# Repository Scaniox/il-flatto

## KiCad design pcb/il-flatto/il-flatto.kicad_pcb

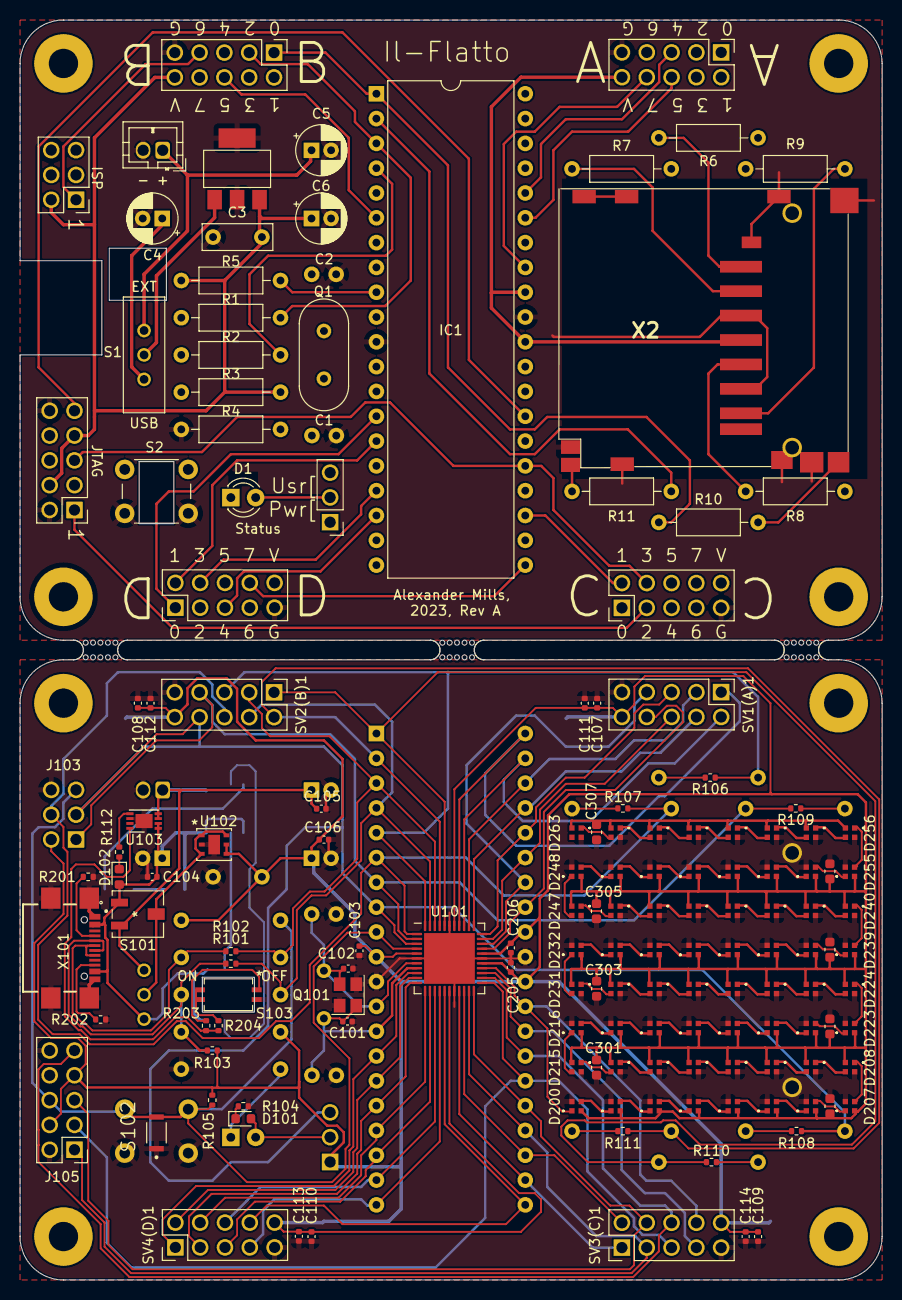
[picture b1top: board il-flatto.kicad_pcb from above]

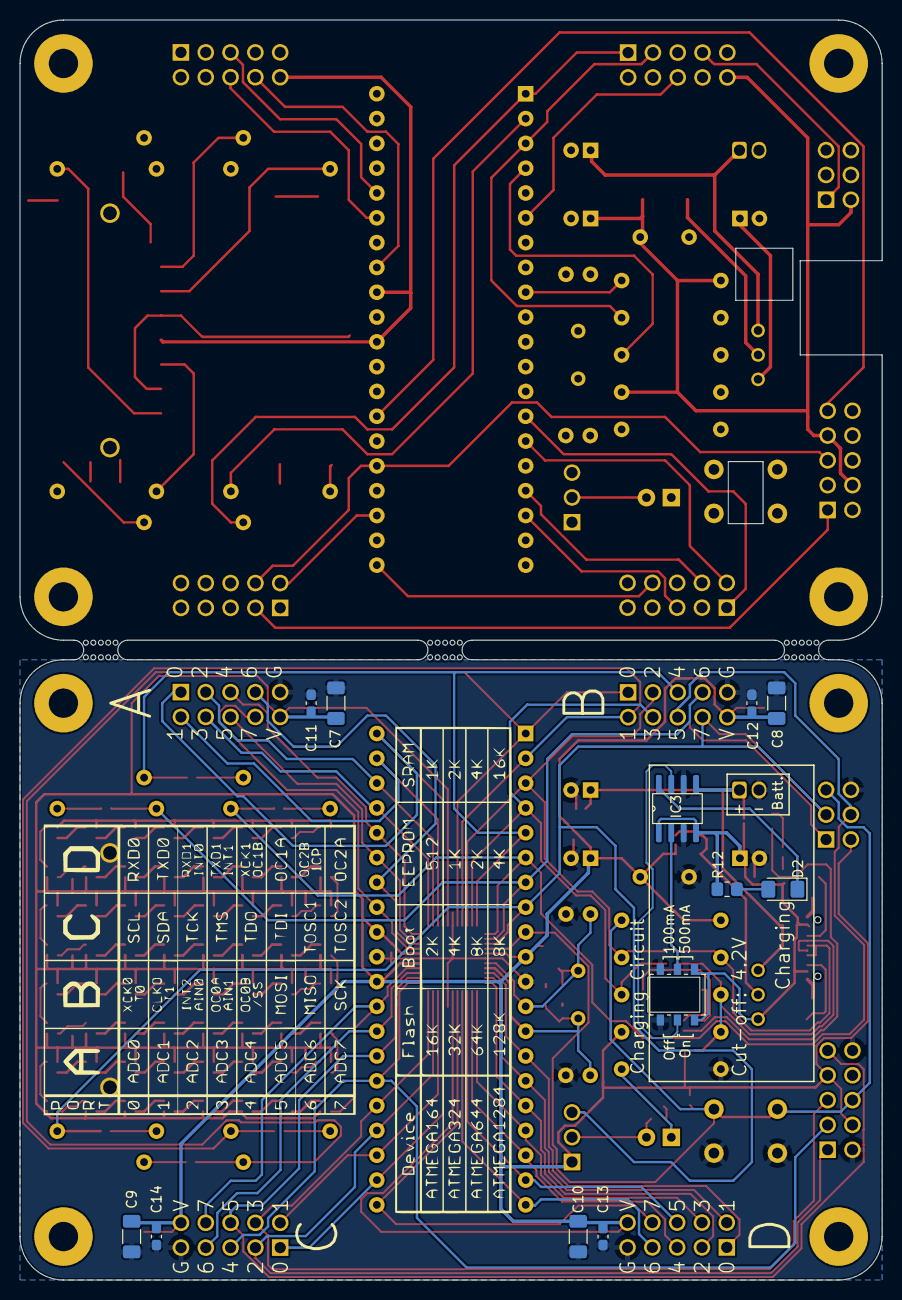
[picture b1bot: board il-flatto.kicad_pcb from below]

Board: 2 copper layers, 88.3 x 129.0 mm, 191 parts (12 on the bottom side), 126 nets.

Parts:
C1, C1#2, C2, C2#2: 22pf; C_Disc_D3.8mm_W2.6mm_P2.50mm
C3, C3#2: 100nf; C_Disc_D7.0mm_W2.5mm_P5.00mm
C4, C4#2, C5, C5#2: 10uf; CP_Radial_D5.0mm_P2.00mm
C6, C6#2: 100uf; CP_Radial_D5.0mm_P2.00mm
C7, C8, C9, C10: 10uf; C_1206_3216Metric_Pad1.33x1.80mm_HandSolder
C11, C12, C13, C14: 100nf; C_0603_1608Metric_Pad1.08x0.95mm_HandSolder
C101, C102: 22pf; C_0402_1005Metric
C103, C111, C112, C113, C114, C205, C206: 100nf; C_0402_1005Metric
C104, C105, C106, C107, C108, C109, C110: 10uf; C_0402_1005Metric
C300, C301, C302, C303, C304, C305, C306, C307: 10u; C_0603_1608Metric
D1, D1#2: LED; LED_D3.0mm
D2: CHRG; LED_1206_3216Metric_Pad1.42x1.75mm_HandSolder
D101: LED; LED_0603_1608Metric
D102: CHRG; LED_0603_1608Metric
D200, D201, D202, D203, D204, D205, D206, D207, D208, D209, D210, D211, D212, D213, D214, D215, D216, D217, D218, D219, D220, D221, D222, D223, D224, D225, D226, D227, D228, D229, D230, D231, D232, D233, D234, D235, D236, D237, D238, D239, D240, D241, D242, D243, D244, D245, D246, D247, D248, D249, D250, D251, D252, D253, D254, D255, D256, D257, D258, D259, D260, D261, D262, D263: IN-PI15TAT5R5G5B; INPI15TAT5R5G5B
IC1: ATmega1284P-P; DIP-40_W15.24mm
IC2: MCP1825S; SOT-223-3_TabPin2
IC3: MAX1811; SOIC-8_3.9x4.9mm_P1.27mm
J3, J103: ISP; PinSocket_2x03_P2.54mm zero footprint mirror
J5, J105: JTAG; PinSocket_2x05_P2.54mm zero footprint mirror
JP3, JP103: Conn_01x03; PinHeader_1x03_P2.54mm zero footprint
Q1, Q1#2: 12MHz; Crystal_HC49-4H_Vertical
Q101: 12MHz; Crystal_SMD_Abracon_ABM8G-4Pin_3.2x2.5mm
R1, R1#2, R2, R2#2, R6, R6#2, R7, R7#2, R8, R8#2, R9, R9#2, R10, R10#2, R11, R11#2: 68; R_Axial_DIN0207_L6.3mm_D2.5mm_P10.16mm_Horizontal
R3, R3#2: 1.5k; R_Axial_DIN0207_L6.3mm_D2.5mm_P10.16mm_Horizontal
R4, R4#2: 220; R_Axial_DIN0207_L6.3mm_D2.5mm_P10.16mm_Horizontal
R5, R5#2: 10k; R_Axial_DIN0207_L6.3mm_D2.5mm_P10.16mm_Horizontal
R12: 330; R_0805_2012Metric_Pad1.20x1.40mm_HandSolder
R101, R102, R106, R107, R108, R109, R110, R111: 68; R_0402_1005Metric
R103: 1.5k; R_0402_1005Metric
R104: 220; R_0402_1005Metric
R105, R204: 10k; R_0402_1005Metric
R112: 470; R_0402_1005Metric
R201, R202: 5.1k; R_0402_1005Metric
R203: 2.5k; R_0402_1005Metric
S1, S1#2: S1; EG1218
S2, S2#2: SW_SPST; SW_PUSH_6mm
S3: 0; CAS-D20TB
S101: PWR SEL; CS-4-12XA
S102: SW_SPST; SW_TL3780AF240QG
S103: SW_DPST_x2; CVS-02TB mirrored
SV1(A)1, SV1(A)1#2, SV2(B)1, SV2(B)1#2, SV3(C)1, SV3(C)1#2, SV4(D)1, SV4(D)1#2: Conn_02x05_Odd_Even; PinSocket_2x05_P2.54mm zero footprint mirror
U101: ATmega1284P-M; QFN-44-1EP_7x7mm_P0.5mm_EP5.2x5.2mm
U102: NCV8605MN33T2G
U103: MCP73831-2-MC; DFN-8-1EP_3x2mm_P0.5mm_EP1.75x1.45mm
X2, X102: SD_Card; sd card
X3, X103: BAT; JST_PH_B2B-PH-K_1x02_P2.00mm_Vertical
X101: USB_C_Receptacle_USB2.0; GCT_USB4110-GF-A_REVB
mouse-bite-3mm-slot, mouse-bite-3mm-slot#2, mouse-bite-3mm-slot#3: VAL**; mouse-bite-3mm-slot

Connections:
/internals/Row1/DOUT: D207.1 (DOUT), D208.3 (DIN)
/internals/Row2/DOUT: D215.1 (DOUT), D216.3 (DIN)
/internals/Row3/DOUT: D223.1 (DOUT), D224.3 (DIN)
/internals/Row4/DOUT: D231.1 (DOUT), D232.3 (DIN)
/internals/Row5/DOUT: D239.1 (DOUT), D240.3 (DIN)
/internals/Row6/DOUT: D247.1 (DOUT), D248.3 (DIN)
/internals/Row7/DOUT: D255.1 (DOUT), D256.3 (DIN)
GND: C1.1, C1#2.1, C2.1, C2#2.1, C3.2, C3#2.2, C4.2, C4#2.2, C5.2, C5#2.2, C6.2, C6#2.2, C7.2, C8.2, C9.2, C10.2, C11.2, C12.2, C13.2, C14.2, C101.1, C102.1, C103.2, C104.1, C105.1, C106.1, C107.2, C108.2, C109.2, C110.2, C111.2, C112.2, C113.2, C114.2, C205.2, C206.2, C300.2, C301.2, C302.2, C303.2, C304.2, C305.2, C306.2, C307.2, D200.4 (VSS), D201.4 (VSS), D202.4 (VSS), D203.4 (VSS), D204.4 (VSS), D205.4 (VSS), D206.4 (VSS), D207.4 (VSS), D208.4 (VSS), D209.4 (VSS), D210.4 (VSS), D211.4 (VSS), D212.4 (VSS), D213.4 (VSS), D214.4 (VSS), D215.4 (VSS), D216.4 (VSS), D217.4 (VSS), D218.4 (VSS), D219.4 (VSS), D220.4 (VSS), D221.4 (VSS), D222.4 (VSS), D223.4 (VSS), D224.4 (VSS), D225.4 (VSS), D226.4 (VSS), D227.4 (VSS), D228.4 (VSS), D229.4 (VSS), D230.4 (VSS), D231.4 (VSS), D232.4 (VSS), D233.4 (VSS), D234.4 (VSS), D235.4 (VSS), D236.4 (VSS), D237.4 (VSS), D238.4 (VSS), D239.4 (VSS), D240.4 (VSS), D241.4 (VSS), D242.4 (VSS), D243.4 (VSS), D244.4 (VSS), D245.4 (VSS), D246.4 (VSS), D247.4 (VSS), D248.4 (VSS), D249.4 (VSS), D250.4 (VSS), D251.4 (VSS), D252.4 (VSS), D253.4 (VSS), D254.4 (VSS), D255.4 (VSS), D256.4 (VSS), D257.4 (VSS), D258.4 (VSS), D259.4 (VSS), D260.4 (VSS), D261.4 (VSS), D262.4 (VSS), D263.4 (VSS), IC1.11 (GND), IC1.31 (GND), IC2.2 (GND), IC3.3 (GND), IC3.6 (GND), J3.6, J5.2, J5.10, J103.6, J105.2, J105.10, Q101.2, Q101.4, R4.2, R4#2.2, R104.2, R201.2, R202.2, S2.1 (A), S2#2.1 (A), S3.1 (A), S3.4 (A), S102.1 (A), S103.3 (A), SV1(A)1.9, SV1(A)1#2.9, SV2(B)1.9, SV2(B)1#2.9, SV3(C)1.9, SV3(C)1#2.9, SV4(D)1.9, SV4(D)1#2.9, U101.6 (GND), U101.18 (GND), U101.28 (GND), U101.39 (GND), U101.45 (GND), U102.2 (GND), U102.7 (EPAD), U103.6 (VSS), X2.3 (VSS), X2.6 (VSS), X2.13 (SHELL2), X3.2, X101.A1/B12 (GND), X101.B1/A12 (GND), X101.S1 (SHIELD), X101.S2 (SHIELD), X101.S3 (SHIELD), X101.S4 (SHIELD), X103.2
LDO_in: IC2.1 (VI), S1.2 (B), S1#2.2 (B), S101.2 (B), U102.1 (VIN), U102.3 (NC/EN), U102.6 (VIN)
unnamed: D1.1 (K), D1#2.1 (K), R4.1, R4#2.1
unnamed: D1.2 (A), D1#2.2 (A), JP3.2
unnamed: D2.1 (K), IC3.8 (~CHG)
unnamed: D2.2 (A), R12.2
unnamed: D101.1 (K), R104.1
unnamed: D101.2 (A), JP103.2
unnamed: D102.1 (K), R112.1
unnamed: D200.1 (DOUT), D201.3 (DIN)
unnamed: D201.1 (DOUT), D202.3 (DIN)
unnamed: D202.1 (DOUT), D203.3 (DIN)
unnamed: D203.1 (DOUT), D204.3 (DIN)
unnamed: D204.1 (DOUT), D205.3 (DIN)
unnamed: D205.1 (DOUT), D206.3 (DIN)
unnamed: D206.1 (DOUT), D207.3 (DIN)
unnamed: D208.1 (DOUT), D209.3 (DIN)
unnamed: D209.1 (DOUT), D210.3 (DIN)
unnamed: D210.1 (DOUT), D211.3 (DIN)
unnamed: D211.1 (DOUT), D212.3 (DIN)
unnamed: D212.1 (DOUT), D213.3 (DIN)
unnamed: D213.1 (DOUT), D214.3 (DIN)
unnamed: D214.1 (DOUT), D215.3 (DIN)
unnamed: D216.1 (DOUT), D217.3 (DIN)
unnamed: D217.1 (DOUT), D218.3 (DIN)
unnamed: D218.1 (DOUT), D219.3 (DIN)
unnamed: D219.1 (DOUT), D220.3 (DIN)
unnamed: D220.1 (DOUT), D221.3 (DIN)
unnamed: D221.1 (DOUT), D222.3 (DIN)
unnamed: D222.1 (DOUT), D223.3 (DIN)
unnamed: D224.1 (DOUT), D225.3 (DIN)
unnamed: D225.1 (DOUT), D226.3 (DIN)
unnamed: D226.1 (DOUT), D227.3 (DIN)
unnamed: D227.1 (DOUT), D228.3 (DIN)
unnamed: D228.1 (DOUT), D229.3 (DIN)
unnamed: D229.1 (DOUT), D230.3 (DIN)
unnamed: D230.1 (DOUT), D231.3 (DIN)
unnamed: D232.1 (DOUT), D233.3 (DIN)
unnamed: D233.1 (DOUT), D234.3 (DIN)
unnamed: D234.1 (DOUT), D235.3 (DIN)
unnamed: D235.1 (DOUT), D236.3 (DIN)
unnamed: D236.1 (DOUT), D237.3 (DIN)
unnamed: D237.1 (DOUT), D238.3 (DIN)
unnamed: D238.1 (DOUT), D239.3 (DIN)
unnamed: D240.1 (DOUT), D241.3 (DIN)
unnamed: D241.1 (DOUT), D242.3 (DIN)
unnamed: D242.1 (DOUT), D243.3 (DIN)
unnamed: D243.1 (DOUT), D244.3 (DIN)
unnamed: D244.1 (DOUT), D245.3 (DIN)
unnamed: D245.1 (DOUT), D246.3 (DIN)
unnamed: D246.1 (DOUT), D247.3 (DIN)
unnamed: D248.1 (DOUT), D249.3 (DIN)
unnamed: D249.1 (DOUT), D250.3 (DIN)
unnamed: D250.1 (DOUT), D251.3 (DIN)
unnamed: D251.1 (DOUT), D252.3 (DIN)
unnamed: D252.1 (DOUT), D253.3 (DIN)
unnamed: D253.1 (DOUT), D254.3 (DIN)
unnamed: D254.1 (DOUT), D255.3 (DIN)
unnamed: D256.1 (DOUT), D257.3 (DIN)
unnamed: D257.1 (DOUT), D258.3 (DIN)
unnamed: D258.1 (DOUT), D259.3 (DIN)
unnamed: D259.1 (DOUT), D260.3 (DIN)
unnamed: D260.1 (DOUT), D261.3 (DIN)
unnamed: D261.1 (DOUT), D262.3 (DIN)
unnamed: D262.1 (DOUT), D263.3 (DIN)
unnamed: IC3.2 (SELI), S3.5 (B)
unnamed: IC3.7 (EN), S3.2 (B)
unnamed: R6.2, R6#2.2, X2.1 (CD/DAT3)
unnamed: R7.1, R7#2.1, X2.2 (CMD)
unnamed: R8.1, R8#2.1, X2.5 (CLK)
unnamed: R9.1, R9#2.1, X2.7 (DAT0)
unnamed: R10.2, R10#2.2, X2.11 (WRITE_PROTECT)
unnamed: R11.1, R11#2.1, X2.10 (CARD_DETECT)
unnamed: R112.2, U103.5 (STAT)
unnamed: R201.1, X101.A5 (CC1)
unnamed: R202.1, X101.B5 (CC2)
unnamed: R203.1, R204.1, U103.8 (PROG)
unnamed: R203.2, S103.1 (A)
unnamed: R204.2, S103.2 (B), S103.4 (B)
PA0: IC1.40 (PA0), SV1(A)1.1, SV1(A)1#2.1, U101.37 (PA0)
PA1: IC1.39 (PA1), SV1(A)1.2, SV1(A)1#2.2, U101.36 (PA1)
PA2: IC1.38 (PA2), SV1(A)1.3, SV1(A)1#2.3, U101.35 (PA2)
PA3: IC1.37 (PA3), SV1(A)1.4, SV1(A)1#2.4, U101.34 (PA3)
PA4: IC1.36 (PA4), SV1(A)1.5, SV1(A)1#2.5, U101.33 (PA4)
PA5: IC1.35 (PA5), SV1(A)1.6, SV1(A)1#2.6, U101.32 (PA5)
PA6: IC1.34 (PA6), SV1(A)1.7, SV1(A)1#2.7, U101.31 (PA6)
PA7: IC1.33 (PA7), SV1(A)1.8, SV1(A)1#2.8, U101.30 (PA7)
PB0: IC1.1 (PB0), R10.1, R10#2.1, R110.1, SV2(B)1.1, SV2(B)1#2.1, U101.40 (PB0)
PB1: IC1.2 (PB1), R11.2, R11#2.2, R111.2, SV2(B)1.2, SV2(B)1#2.2, U101.41 (PB1)
PB2: IC1.3 (PB2), R1.2, R1#2.2, R101.1, SV2(B)1.3, SV2(B)1#2.3, U101.42 (PB2)
PB3: IC1.4 (PB3), R2.1, R2#2.1, R102.2, SV2(B)1.4, SV2(B)1#2.4, U101.43 (PB3)
PB4: IC1.5 (PB4), R6.1, R6#2.1, R106.1, SV2(B)1.5, SV2(B)1#2.5, U101.44 (PB4)
PB5: IC1.6 (PB5), J3.4, J103.4, R7.2, R7#2.2, R107.2, SV2(B)1.6, SV2(B)1#2.6, U101.1 (PB5)
PB6: IC1.7 (PB6), J3.1, J103.1, R9.2, R9#2.2, R109.2, SV2(B)1.7, SV2(B)1#2.7, U101.2 (PB6)
PB7: IC1.8 (PB7), J3.3, J103.3, JP3.3, JP103.3, R8.2, R8#2.2, R108.2, SV2(B)1.8, SV2(B)1#2.8, U101.3 (PB7)
PC0: IC1.22 (PC0), SV3(C)1.1, SV3(C)1#2.1, U101.19 (PC0)
PC1: IC1.23 (PC1), SV3(C)1.2, SV3(C)1#2.2, U101.20 (PC1)
PC2: IC1.24 (PC2), J5.1, J105.1, SV3(C)1.3, SV3(C)1#2.3, U101.21 (PC2)
PC3: IC1.25 (PC3), J5.5, J105.5, SV3(C)1.4, SV3(C)1#2.4, U101.22 (PC3)
PC4: IC1.26 (PC4), J5.3, J105.3, SV3(C)1.5, SV3(C)1#2.5, U101.23 (PC4)
PC5: IC1.27 (PC5), J5.9, J105.9, SV3(C)1.6, SV3(C)1#2.6, U101.24 (PC5)
PC6: IC1.28 (PC6), SV3(C)1.7, SV3(C)1#2.7, U101.25 (PC6)
PC7: D200.3 (DIN), IC1.29 (PC7), SV3(C)1.8, SV3(C)1#2.8, U101.26 (PC7)
PD0: IC1.14 (PD0), SV4(D)1.1, SV4(D)1#2.1, U101.9 (PD0)
PD1: IC1.15 (PD1), SV4(D)1.2, SV4(D)1#2.2, U101.10 (PD1)
PD2: IC1.16 (PD2), SV4(D)1.3, SV4(D)1#2.3, U101.11 (PD2)
PD3: IC1.17 (PD3), SV4(D)1.4, SV4(D)1#2.4, U101.12 (PD3)
PD4: IC1.18 (PD4), SV4(D)1.5, SV4(D)1#2.5, U101.13 (PD4)
PD5: IC1.19 (PD5), SV4(D)1.6, SV4(D)1#2.6, U101.14 (PD5)
PD6: IC1.20 (PD6), SV4(D)1.7, SV4(D)1#2.7, U101.15 (PD6)
PD7: IC1.21 (PD7), SV4(D)1.8, SV4(D)1#2.8, U101.16 (PD7)
Q1_1: C1.2, C1#2.2, C101.2, IC1.13 (XTAL1), Q1.2, Q1#2.2, Q101.1, U101.8 (XTAL1)
Q1_2: C2.2, C2#2.2, C102.2, IC1.12 (XTAL2), Q1.1, Q1#2.1, Q101.3, U101.7 (XTAL2)
USB D+: R1.1, R1#2.1, R101.2, X101.A6 (D+), X101.B6 (D+)
USB D-: R2.2, R2#2.2, R3.2, R3#2.2, R102.1, R103.2, X101.A7 (D-), X101.B7 (D-)
VBUS: C4.1, C4#2.1, C104.2, D102.2 (A), IC3.1 (SELV), IC3.4 (IN), R12.1, S1.1 (A), S1#2.1 (A), S3.3 (C), S3.6 (C), S101.1 (A), U103.1 (VDD), U103.2 (VDD), X101.A4/B9 (VBUS), X101.B4/A9 (VBUS)
VDD: C3.1, C3#2.1, C6.1, C6#2.1, C7.1, C8.1, C9.1, C10.1, C11.1, C12.1, C13.1, C14.1, C103.1, C106.2, C107.1, C108.1, C109.1, C110.1, C111.1, C112.1, C113.1, C114.1, C205.1, C206.1, C300.1, C301.1, C302.1, C303.1, C304.1, C305.1, C306.1, C307.1, D200.2 (VDD), D201.2 (VDD), D202.2 (VDD), D203.2 (VDD), D204.2 (VDD), D205.2 (VDD), D206.2 (VDD), D207.2 (VDD), D208.2 (VDD), D209.2 (VDD), D210.2 (VDD), D211.2 (VDD), D212.2 (VDD), D213.2 (VDD), D214.2 (VDD), D215.2 (VDD), D216.2 (VDD), D217.2 (VDD), D218.2 (VDD), D219.2 (VDD), D220.2 (VDD), D221.2 (VDD), D222.2 (VDD), D223.2 (VDD), D224.2 (VDD), D225.2 (VDD), D226.2 (VDD), D227.2 (VDD), D228.2 (VDD), D229.2 (VDD), D230.2 (VDD), D231.2 (VDD), D232.2 (VDD), D233.2 (VDD), D234.2 (VDD), D235.2 (VDD), D236.2 (VDD), D237.2 (VDD), D238.2 (VDD), D239.2 (VDD), D240.2 (VDD), D241.2 (VDD), D242.2 (VDD), D243.2 (VDD), D244.2 (VDD), D245.2 (VDD), D246.2 (VDD), D247.2 (VDD), D248.2 (VDD), D249.2 (VDD), D250.2 (VDD), D251.2 (VDD), D252.2 (VDD), D253.2 (VDD), D254.2 (VDD), D255.2 (VDD), D256.2 (VDD), D257.2 (VDD), D258.2 (VDD), D259.2 (VDD), D260.2 (VDD), D261.2 (VDD), D262.2 (VDD), D263.2 (VDD), IC1.10 (VCC), IC1.30 (AVCC), IC1.32 (AREF), IC2.3 (VO), J3.2, J5.4, J5.7, J103.2, J105.4, J105.7, JP3.1, JP103.1, R3.1, R3#2.1, R5.1, R5#2.1, R103.1, R105.1, SV1(A)1.10, SV1(A)1#2.10, SV2(B)1.10, SV2(B)1#2.10, SV3(C)1.10, SV3(C)1#2.10, SV4(D)1.10, SV4(D)1#2.10, U101.5 (VCC), U101.17 (VCC), U101.27 (AVCC), U101.29 (AREF), U101.38 (VCC), U102.4 (VOUT), U102.5 (SENSE/ADJ), X2.4 (VDD)
V_BAT: C5.1, C5#2.1, C105.2, IC3.5 (BATT), S1.3 (C), S1#2.3 (C), S101.3 (C), U103.3 (VBAT), U103.4 (VBAT), X3.1, X103.1
n_reset: IC1.9 (~RESET), J3.5, J5.6, J103.5, J105.6, R5.2, R5#2.2, R105.2, S2.2 (B), S2#2.2 (B), S102.2 (B), U101.4 (~RESET)

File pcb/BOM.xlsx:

Id | Designator | Package | populate | Quantity | Designation | Supplier | link | ordered | acquired
20 | ,,,,, |  |  | 6
38 | C1,C2,C2,C1 | C_Disc_D3.8mm_W2.6mm_P2.50mm |  | 4 | 22pf
10 | C102,C101 | C_0402_1005Metric | x | 2 | 22pf | have
14 | C108,C110,C107,C109,C106,C105,C104 | C_0402_1005Metric | x | 7 | 10uf | have
6 | C113,C205,C111,C112,C103,C114,C206 | C_0402_1005Metric | x | 7 | 100nf | have
44 | C13,C14,C11,C12 | C_0603_1608Metric_Pad1.08x0.95mm_HandSolder |  | 4 | 100nf
21 | C3,C3 | C_Disc_D7.0mm_W2.5mm_P5.00mm |  | 2 | 100nf
4 | C304,C303,C305,C307,C306,C302,C301,C300 | C_0603_1608Metric | x | 8 | 10uf | digikey | https://www.digikey.com/en/products/detail/murata-electronic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 | x
8 | C4,C5,C4,C5 | CP_Radial_D5.0mm_P2.00mm |  | 4 | 10uf
5 | C6,C6 | CP_Radial_D5.0mm_P2.00mm |  | 2 | 100uf
47 | C7,C9,C8,C10 | C_1206_3216Metric_Pad1.33x1.80mm_HandSolder |  | 4 | 10uf
33 | D1,D1 | LED_D3.0mm |  | 2 | LED
42 | D101 | LED_0603_1608Metric | x | 1 | LED | have
35 | D102 | LED_0603_1608Metric | x | 1 | CHRG | have
46 | D2 | LED_1206_3216Metric_Pad1.42x1.75mm_HandSolder |  | 1 | CHRG
2 | D210,D211,D232,D258,D250,D249,D261,D252,D227,D200,D221,D231,D206,D201,D233,D253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 | IN-PI15TAT5R5G5B | x | 64 | IN-PI15TAT5R5G5B | digikey | https://www.digikey.co.uk/en/products/detail/inolux/IN-PI15T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 | x
29 | IC1 | DIP-40_W15.24mm |  | 1 | ATmega1284P-P
34 | IC2 | SOT-223-3_TabPin2 |  | 1 | MCP1825S
49 | IC3 | SOIC-8_3.9x4.9mm_P1.27mm |  | 1 | MAX1811
40 | J3 | PinSocket_2x03_P2.54mm zero footprint mirror |  | 1 | ISP
26 | J5 | PinSocket_2x05_P2.54mm zero footprint mirror |  | 1 | JTAG
18 | JP3,JP103 | PinHeader_1x03_P2.54mm zero footprint |  | 2 | Conn_01x03
9 | Q1,Q1 | Crystal_HC49-4H_Vertical |  | 2 | 12MHz
37 | Q101 | Crystal_SMD_Abracon_ABM8G-4Pin_3.2x2.5mm | x | 1 | 12MHz | digikey | https://www.digikey.com/en/products/detail/abracon-llc/ABM8G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 | x
1 | R1,R10,R2,R9,R8,R9,R2,R1,R10,R7,R8,R11,R6,R11,R7,R6 | R_Axial_DIN0207_L6.3mm_D2.5mm_P10.16mm_Horizontal |  | 16 | 68
32 | R103 | R_0402_1005Metric | x | 1 | 1.5k | digikey | https://www.digikey.com/en/products/detail/walsin-technology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 | x
41 | R104 | R_0402_1005Metric | x | 1 | 220 | digikey | https://www.digikey.com/en/products/detail/walsin-technology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 | x
3 | R110,R107,R101,R106,R111,R109,R108,R102 | R_0402_1005Metric | x | 8 | 68 | digikey | https://www.digikey.com/en/products/detail/walsin-technology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 | x
27 | R112 | R_0402_1005Metric | x | 1 | 470 | have
48 | R12 | R_0805_2012Metric_Pad1.20x1.40mm_HandSolder |  | 1 | 330
17 | R202,R201 | R_0402_1005Metric | x | 2 | 5.1k | digikey | https://www.digikey.co.uk/en/products/detail/yageo/RC0402FR-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 | x
23 | R203 | R_0402_1005Metric | x | 1 | 2.5k | digikey | https://www.digikey.co.uk/en/products/detail/yageo/RC0402FR-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 | x
24 | R204,R105 | R_0402_1005Metric | x | 2 | 10k | have
19 | R3,R3 | R_Axial_DIN0207_L6.3mm_D2.5mm_P10.16mm_Horizontal |  | 2 | 1.5k
13 | R4,R4 | R_Axial_DIN0207_L6.3mm_D2.5mm_P10.16mm_Horizontal |  | 2 | 220
31 | R5,R5 | R_Axial_DIN0207_L6.3mm_D2.5mm_P10.16mm_Horizontal |  | 2 | 10k
22 | S1,S1 | EG1218 |  | 2 | S1
43 | S101 | CS-4-12XA | x | 1 | PWR SEL | digikey | https://www.digikey.co.uk/en/products/detail/nidec-copal-ele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 | x
16 | S102 | SW_TL3780AF240QG | x | 1 | SW_SPST | digikey | https://www.digikey.co.uk/en/products/detail/e-switch/TL3780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 | x
28 | S103 | CVS-02TB mirrored | x | 1 | SW_DPST_x2 | digikey | https://www.digikey.co.uk/en/products/detail/nidec-copal-ele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 | x
39 | S2,S2 | SW_PUSH_6mm |  | 2 | SW_SPST
45 | S3 | CAS-D20TB |  | 1 | 0
1 | SV[1-4] , J5, J3, X3 | Mill-max 0531-0-15-15-31-27-10-0 | x | 61 | 0531-0-15-15-31-27-10-0 | digikey | https://www.digikey.co.uk/en/products/detail/mill-max-manufa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 | x
7 | SV1(A)1,SV3(C)1,SV1(A)1,SV4(D)1,SV3(C)1,SV2(B)1,SV4(D)1,SV2(B)1 | PinSocket_2x05_P2.54mm zero footprint mirror |  | 8 | Conn_02x05_Odd_Even
15 | U101 | QFN-44-1EP_7x7mm_P0.5mm_EP5.2x5.2mm | x | 1 | ATmega1284P-M | bruh
11 | U102 | NCV8605MN33T2G | x | 1 | NCV8605MN33T2G | digikey | https://www.digikey.com/en/products/detail/onsemi/NCV8605MN3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 | x
30 | U103 | DFN-8-1EP_3x2mm_P0.5mm_EP1.75x1.45mm | x | 1 | MCP73831-2-MC | digikey | https://www.digikey.co.uk/en/products/detail/microchip-techn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 | x
12 | X101 | GCT_USB4110-GF-A_REVB | x | 1 | USB_C_Receptacle_USB2.0 | digikey | https://www.digikey.co.uk/en/products/detail/gct/USB4110-GF-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 | x
25 | X102,X2 | sd card |  | 2 | SD_Card
36 | X3 | JST_PH_B2B-PH-K_1x02_P2.00mm_Vertical |  | 1 | BAT

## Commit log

2022-12-18 bootloader progress
2022-12-21 simple il matto done
2023-01-02 good to go?
2023-01-09 changed to 1.5mm RGBLEDs because cheaper
2023-12-19 messing around
2024-01-26 much bootloader doings
2024-01-26 1284 starts in the right place, but can't find descriptors
2024-01-28 botched descriptor make 1284p enumerate
2024-01-28 about to test symbols
2024-01-28 some relabeling
2024-01-28 Revert labeling part of "some relabeling"
    This reverts labeling part of commit bbd5bf2ad99073f805421d0d658776fe1fbc92f9.
2024-01-28 automated relabeling done
2024-01-28 ram map
2024-01-29 bodged in rampz-age makes it enumerate
2024-01-29 technically works now
2024-01-29 pcb file format update to kicad7
2024-01-29 ibom ready to go
2024-01-29 organise build artefacts
2024-01-30 build gubbins

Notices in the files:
parts and their libraries:
Copyright 2021 Accelerated Designs. All rights reserved.
